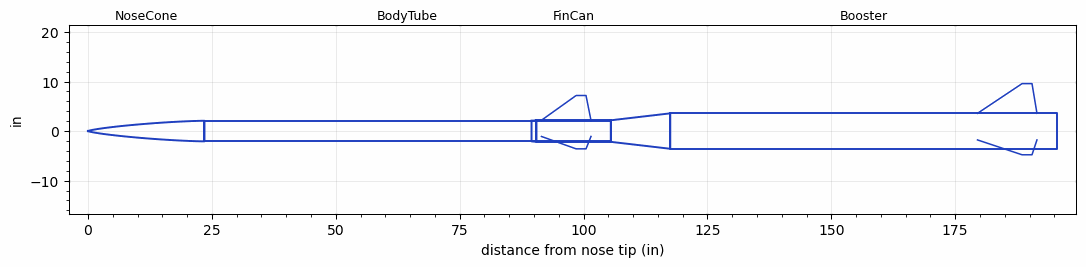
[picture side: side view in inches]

<RASAeroDocument>
 <FileVersion>2</FileVersion>
 <RocketDesign>
  <NoseCone>
   <Length>23.5</Length>
   <Diameter>4.153</Diameter>
   <Shape>Von Karman Ogive</Shape>
   <BluntRadius>0.0625</BluntRadius>
   <Location>0</Location>
  </NoseCone>
  <BodyTube>
   <Length>82</Length>
   <Diameter>4.153</Diameter>
   <Location>23.5</Location>
  </BodyTube>
  <FinCan>
   <Length>15</Length>
   <Diameter>4.353</Diameter>
   <InsideDiameter>4.153</InsideDiameter>
   <Location>105.5</Location>
   <ShoulderLength>1</ShoulderLength>
   <Offset>-15</Offset>
   <Fin>
    <Count>3</Count>
    <Chord>10</Chord>
    <Span>5</Span>
    <SweepDistance>7</SweepDistance>
    <TipChord>2</TipChord>
    <Thickness>0.34</Thickness>
    <LERadius>0.0625</LERadius>
    <Location>14</Location>
    <AirfoilSection>Hexagonal</AirfoilSection>
    <FX1>0.5</FX1>
    <FX3>0.5</FX3>
   </Fin>
  </FinCan>
  <Booster>
   <Length>78</Length>
   <Diameter>7.15</Diameter>
   <InsideDiameter>4.353</InsideDiameter>
   <Location>105.5</Location>
   <ShoulderLength>12</ShoulderLength>
   <Fin>
    <Count>3</Count>
    <Chord>12</Chord>
    <Span>6</Span>
    <SweepDistance>9</SweepDistance>
    <TipChord>2</TipChord>
    <Thickness>0.25</Thickness>
    <LERadius>0.0625</LERadius>
    <Location>16</Location>
    <AirfoilSection>Hexagonal</AirfoilSection>
    <FX1>0.5</FX1>
    <FX3>0.5</FX3>
   </Fin>
  </Booster>
  <Surface>Rough Camouflage Paint</Surface>
  <ModifiedBarrowman>True</ModifiedBarrowman>
  <Turbulence>True</Turbulence>
  <UseBooster1>True</UseBooster1>
  <UseBooster2>False</UseBooster2>
 </RocketDesign>
 <LaunchSite>
  <Altitude>3000</Altitude>
  <Pressure>30.3</Pressure>
  <RodAngle>1</RodAngle>
  <RodLength>18</RodLength>
  <Temperature>90</Temperature>
  <WindSpeed>12</WindSpeed>
 </LaunchSite>
 <Recovery>
  <Altitude1>1000</Altitude1>
  <Altitude2>1000</Altitude2>
  <DeviceType1>None</DeviceType1>
  <DeviceType2>None</DeviceType2>
  <Event1>False</Event1>
  <Event2>False</Event2>
  <Size1>1</Size1>
  <Size2>1</Size2>
  <EventType1>None</EventType1>
  <EventType2>None</EventType2>
  <CD1>1.33</CD1>
  <CD2>1.33</CD2>
 </Recovery>
 <SimulationList>
  <Simulation>
   <SustainerEngine>BERMA-25000-02  (Karman_AIAA-capstone)</SustainerEngine>
   <SustainerLaunchWt>47</SustainerLaunchWt>
   <SustainerNozzleDiameter>3.9</SustainerNozzleDiameter>
   <SustainerCG>69</SustainerCG>
   <SustainerIgnitionDelay>12</SustainerIgnitionDelay>
   <Booster1Engine>O8000  (CTI)</Booster1Engine>
   <Booster1LaunchWt>170</Booster1LaunchWt>
   <Booster1SeparationDelay>0.5</Booster1SeparationDelay>
   <Booster1IgnitionDelay>0</Booster1IgnitionDelay>
   <Booster1CG>123</Booster1CG>
   <Booster1NozzleDiameter>4.8</Booster1NozzleDiameter>
   <IncludeBooster1>True</IncludeBooster1>
   <Booster2Delay>0</Booster2Delay>
   <IncludeBooster2>False</IncludeBooster2>
   <TimetoApogee>165.4615</TimetoApogee>
   <MaxAltitude>369982.2</MaxAltitude>
   <MaxVelocity>5844.149</MaxVelocity>
  </Simulation>
  <Simulation>
   <SustainerEngine>BERMA-25000-02  (Karman_AIAA-capstone)</SustainerEngine>
   <SustainerLaunchWt>45</SustainerLaunchWt>
   <SustainerNozzleDiameter>3.9</SustainerNozzleDiameter>
   <SustainerCG>60</SustainerCG>
   <SustainerIgnitionDelay>23</SustainerIgnitionDelay>
   <Booster1LaunchWt>148</Booster1LaunchWt>
   <Booster1SeparationDelay>0.5</Booster1SeparationDelay>
   <Booster1IgnitionDelay>0</Booster1IgnitionDelay>
   <Booster1CG>105</Booster1CG>
   <Booster1NozzleDiameter>4.8</Booster1NozzleDiameter>
   <IncludeBooster1>False</IncludeBooster1>
   <Booster2Delay>0</Booster2Delay>
   <IncludeBooster2>False</IncludeBooster2>
   <TimetoApogee>60.93578</TimetoApogee>
   <MaxAltitude>80435.52</MaxAltitude>
   <MaxVelocity>4598.493</MaxVelocity>
  </Simulation>
  <Simulation>
   <SustainerEngine>BERMA-25000-02  (Karman_AIAA-capstone)</SustainerEngine>
   <SustainerLaunchWt>45</SustainerLaunchWt>
   <SustainerNozzleDiameter>3.9</SustainerNozzleDiameter>
   <SustainerCG>65</SustainerCG>
   <SustainerIgnitionDelay>10</SustainerIgnitionDelay>
   <Booster1Engine>O3400-IM-P  (CTI)</Booster1Engine>
   <Booster1LaunchWt>145</Booster1LaunchWt>
   <Booster1SeparationDelay>0.5</Booster1SeparationDelay>
   <Booster1IgnitionDelay>0</Booster1IgnitionDelay>
   <Booster1CG>115</Booster1CG>
   <Booster1NozzleDiameter>4.8</Booster1NozzleDiameter>
   <IncludeBooster1>True</IncludeBooster1>
   <Booster2Delay>0</Booster2Delay>
   <IncludeBooster2>False</IncludeBooster2>
   <TimetoApogee>21.04029</TimetoApogee>
   <MaxAltitude>21575.07</MaxAltitude>
   <MaxVelocity>4876.902</MaxVelocity>
  </Simulation>
 </SimulationList>
</RASAeroDocument>
